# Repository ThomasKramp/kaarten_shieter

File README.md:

# kaarten_shieter
The documentation can be found in the .

The PDF was generated using:
- The PDF version of the .md file .
- An online md to pdf converter

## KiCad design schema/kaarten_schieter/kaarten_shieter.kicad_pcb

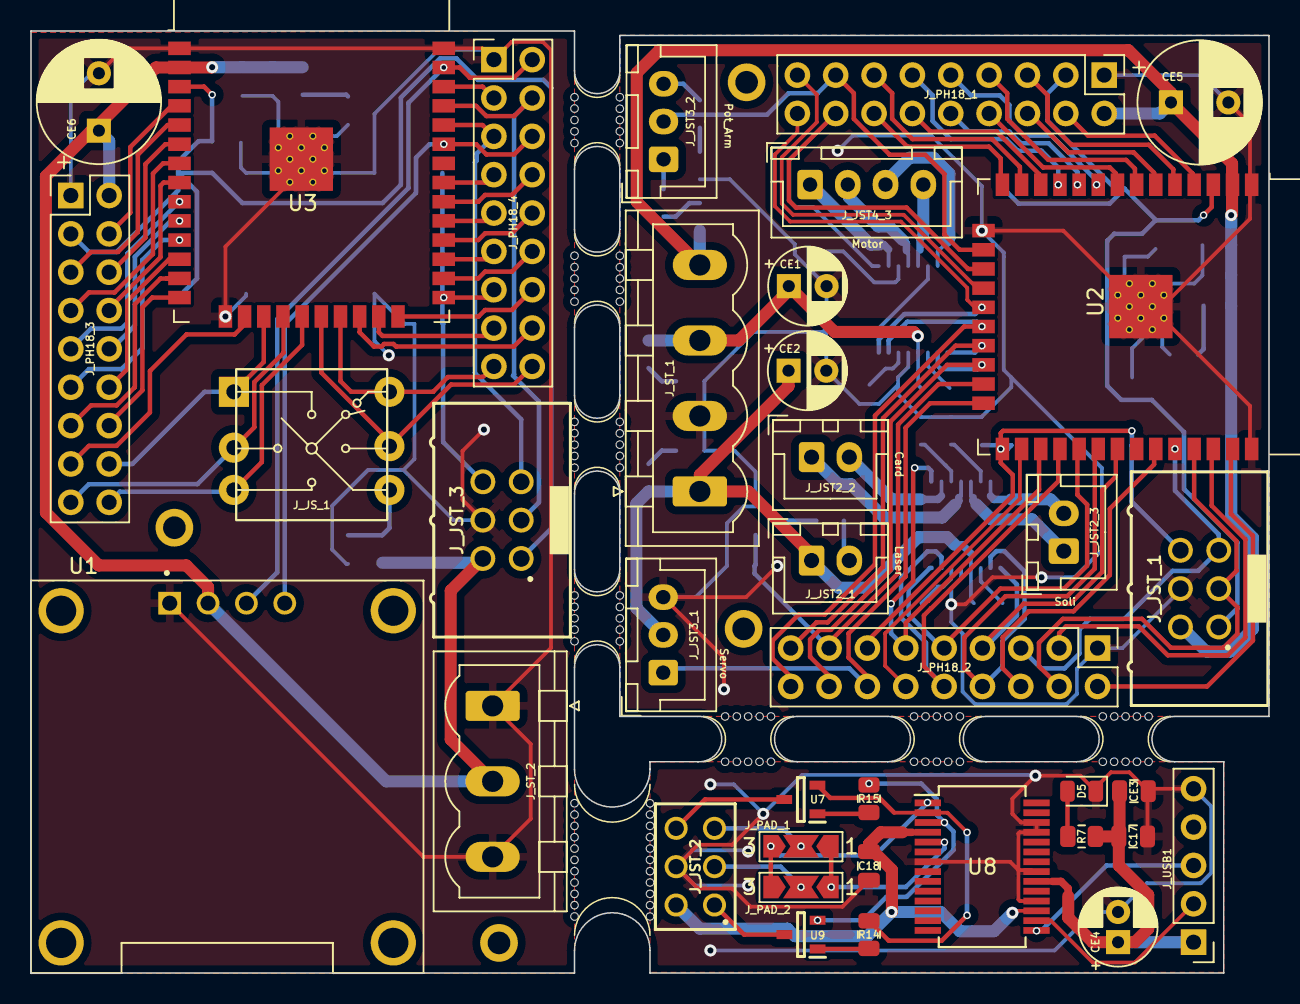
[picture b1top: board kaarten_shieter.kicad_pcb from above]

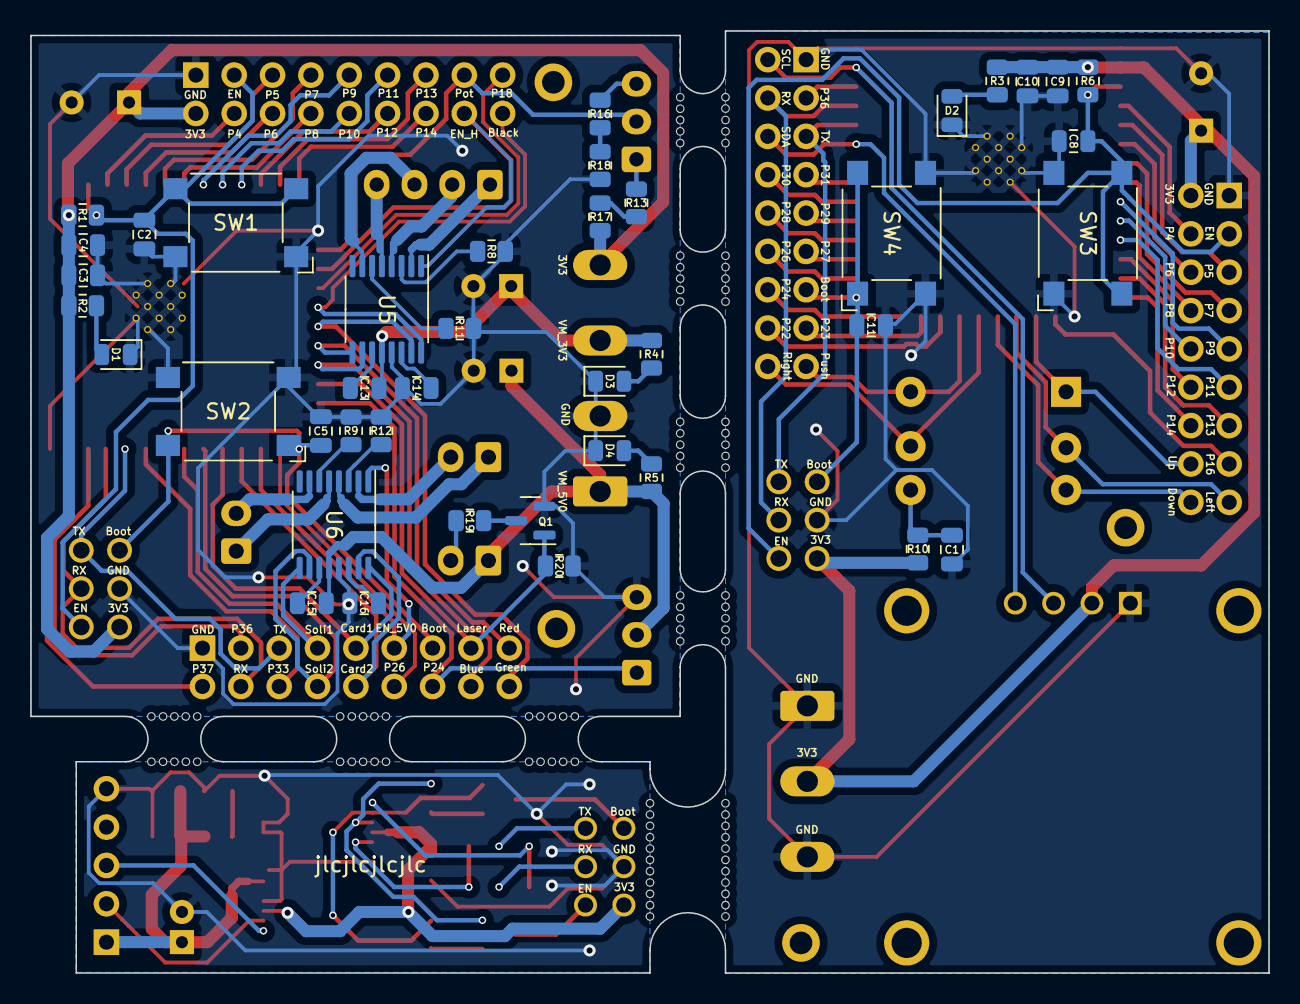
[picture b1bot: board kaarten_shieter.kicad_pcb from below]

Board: 2 copper layers, 82.0 x 62.4 mm, 86 parts (41 on the bottom side), 115 nets.

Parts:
C1, C2, C4, C5, C8, C10, C11: 0u1; C_0805_2012Metric
C3, C9: 22u; C_0805_2012Metric
C13, C15: 0u01; C_0805_2012Metric
C14, C16: 2u2; C_0805_2012Metric
C17, C18: 100n; C_0805_2012Metric
CE1, CE2: 10u; CP_Radial_D5.0mm_P2.50mm
CE3: 10n; C_0805_2012Metric
CE4: 4u7; CP_Radial_D5.0mm_P2.00mm
CE5, CE6: 470u; CP_Radial_D8.0mm_P3.80mm
D1, D2, D3, D4, D5: LED; LED_0805_2012Metric
J_JST2_1, J_JST2_2, J_JST2_3: Conn_01x02_Male; JST_XH_B2B-XH-A_1x02_P2.50mm_Vertical
J_JST3_1, J_JST3_2: Conn_01x03_Male; JST_XH_B3B-XH-A_1x03_P2.50mm_Vertical
J_JST4_3: Conn_01x04_Male; JST_XH_B4B-XH-A_1x04_P2.50mm_Vertical
J_JST_1, J_JST_3: Conn_02x03_Odd_Even; 61200621621
J_JST_2: Conn_02x03_Odd_Even; 61300621821
J_JS_1: Conn_02x03_Counter_Clockwise; JS_SKQUCAA010
J_PAD_1, J_PAD_2: Conn_01x03; SolderJumper-3_P2.0mm_Open_TrianglePad1.0x1.5mm_NumberLabels
J_PH18_1, J_PH18_2, J_PH18_3, J_PH18_4: Conn_02x09_Odd_Even; PinHeader_2x09_P2.54mm_Vertical
J_ST_1: Screw_Terminal_01x04; PhoenixContact_MSTBVA_2,5_4-G_1x04_P5.00mm_Vertical
J_ST_2: Screw_Terminal_01x03; PhoenixContact_MSTBVA_2,5_3-G_1x03_P5.00mm_Vertical
J_USB1: Conn_01x05_Male; PinHeader_1x05_P2.54mm_Vertical
Q1: 2N7002; SOT-23
R1, R6, R10: 10K; R_0805_2012Metric
R2, R3, R4: 1K5; R_0805_2012Metric
R5, R7: 2K; R_0805_2012Metric
R8, R9, R11, R12: 200m; R_0805_2012Metric
R13, R16, R17, R18, R19: R; R_0805_2012Metric
R14, R15: 10k; R_0805_2012Metric
R20: 1M; R_0805_2012Metric
SW1, SW2, SW3, SW4: SW_Push; SW_SPST_Omron_B3FS-100xP
U1: DM-OLED096-636; MODULE_DM-OLED096-636
U2, U3: ESP32-WROOM-32
U5, U6: DRV8833PW; TSSOP-16_4.4x5mm_P0.65mm
U7, U9: BCW71; SOT95P230X110-3N
U8: FT232RL; SSOP-28_5.3x10.2mm_P0.65mm
mouse-bite-5mm-slot, mouse-bite-5mm-slot#3, mouse-bite-5mm-slot#4, mouse-bite-5mm-slot#5, mouse-bite-5mm-slot#6, mouse-bite-5mm-slot#7, mouse-bite-5mm-slot#8: VAL**; mouse-bite-3mm-slot
mouse-bite-5mm-slot#2: VAL**; mouse-bite-5mm-slot

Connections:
3V3_M: C3.1, C4.1, CE5.1, J_JST_1.2, J_PH18_1.2, J_ST_1.4, R1.1, R2.1, R17.1, U2.2 (VDD)
3V3_P: C18.2, J_JST_2.2, U8.4 (VCCIO), U8.17 (3V3OUT)
3V3_R: C9.1, C10.1, CE6.1, J_JST_3.2, J_PH18_3.2, J_ST_2.2, R3.1, R6.1, R10.1, U1.2 (VCC_IN), U3.2 (VDD)
5V0_P: C17.1, CE3.1, CE4.1, J_USB1.1, R7.1, U8.20 (VCC)
BOOT_M: C5.1, J_JST_1.6, J_PH18_2.13, SW2.1, U2.25 (IO0)
BOOT_P: J_JST_2.6, U7.3 (C)
BOOT_R: C11.1, J_JST_3.6, J_PH18_4.13, SW4.1, U3.25 (IO0)
Black: J_JST4_3.1, U5.2 (AOUT1)
Blue: J_JST4_3.4, U5.5 (BOUT2)
CENTER_JS: J_JS_1.6, J_PH18_4.17, U3.21 (SDO/SD0)
COM_JS: C1.1, J_JS_1.4, R10.2
Card1: J_JST2_2.2, U6.2 (AOUT1)
Card2: J_JST2_2.1, U6.4 (AOUT2)
DOWN_JS: J_JS_1.3, J_PH18_3.18, U3.19 (SCS/CMD)
EN_Card: J_PH18_2.11, U2.27 (IO16), U6.1 (nSLEEP)
EN_Hori: J_PH18_1.16, U2.17 (SHD/SD2), U5.1 (nSLEEP)
EN_M: C2.1, J_JST_1.1, J_PH18_1.3, R1.2, SW1.2, U2.3 (EN)
EN_P: J_JST_2.1, U9.3 (C)
EN_R: C8.1, J_JST_3.1, J_PH18_3.3, R6.2, SW3.2, U3.3 (EN)
GND_M: C2.2, C3.2, C4.2, C5.2, C14.1, C16.1, CE1.2, CE2.2, CE5.2, D1.1 (K), D3.1 (K), D4.1 (K), J_JST3_1.3, J_JST_1.4, J_PH18_1.1, J_PH18_2.1, J_ST_1.2, Q1.2 (S), R8.2, R9.2, R11.2, R12.2, R18.1, R20.2, SW1.1, SW2.2, U2.1 (GND), U2.15 (GND), U2.38 (GND), U2.39 (GND), U5.13 (GND), U6.13 (GND)
GND_P: C17.2, C18.1, CE3.2, CE4.2, D5.1 (K), J_JST_2.4, J_USB1.5, U8.7 (GND), U8.18 (GND), U8.21 (GND), U8.25 (AGND), U8.26 (TEST)
GND_R: C1.2, C8.2, C9.2, C10.2, C11.2, CE6.2, D2.1 (K), J_JST_3.4, J_PH18_3.1, J_PH18_4.1, J_ST_2.1, J_ST_2.3, SW3.1, SW4.2, U1.1 (GND), U3.1 (GND), U3.15 (GND), U3.38 (GND), U3.39 (GND)
Green: J_JST4_3.2, U5.4 (AOUT2)
LEFT_JS: J_JS_1.2, J_PH18_3.17, U3.18 (SWP/SD3)
Laser: J_PH18_2.15, Q1.1 (G), R20.1, U2.23 (IO15)
Motor_Card_IN1: J_PH18_2.9, U2.29 (IO5), U6.16 (AIN1)
Motor_Card_IN2: J_PH18_2.10, U2.28 (IO17), U6.15 (AIN2)
Motor_Hori_Black: J_PH18_1.18, U2.19 (SCS/CMD), U5.16 (AIN1)
Motor_Hori_Blue: J_PH18_2.16, U2.22 (SDI/SD1), U5.10 (BIN2)
Motor_Hori_Green: J_PH18_2.18, U2.20 (SCK/CLK), U5.15 (AIN2)
Motor_Hori_Red: J_PH18_2.17, U2.21 (SDO/SD0), U5.9 (BIN1)
Motor_Soli_IN1: J_PH18_2.7, U2.31 (IO19), U6.9 (BIN1)
Motor_Soli_IN2: J_PH18_2.8, U2.30 (IO18), U6.10 (BIN2)
unnamed: C13.2, U5.11 (VCP)
unnamed: C14.2, U5.14 (VINT)
unnamed: C15.2, U6.11 (VCP)
unnamed: C16.2, U6.14 (VINT)
unnamed: D1.2 (A), R2.2
unnamed: D2.2 (A), R3.2
unnamed: D3.2 (A), R4.2
unnamed: D4.2 (A), R5.2
unnamed: D5.2 (A), R7.2
unnamed: J_JST2_1.2, R19.2
unnamed: J_JST3_2.1, R13.2
unnamed: J_JST3_2.3, R16.2
unnamed: Q1.3 (D), R19.1
unnamed: R8.1, U5.3 (AISEN)
unnamed: R9.1, U6.6 (BISEN)
unnamed: R11.1, U5.6 (BISEN)
unnamed: R12.1, U6.3 (AISEN)
unnamed: R13.1, R17.2
unnamed: R14.1, U9.1 (B)
unnamed: R15.1, U7.1 (B)
unnamed: R16.1, R18.2
PIN4_M: J_PH18_1.4, U2.4 (SENSOR_VP)
PIN4_R: J_PH18_3.4, U3.4 (SENSOR_VP)
PIN5_M: J_PH18_1.5, U2.5 (SENSOR_VN)
PIN5_R: J_PH18_3.5, U3.5 (SENSOR_VN)
PIN6_M: J_PH18_1.6, U2.6 (IO34)
PIN6_R: J_PH18_3.6, U3.6 (IO34)
PIN7_M: J_PH18_1.7, U2.7 (IO35)
PIN7_R: J_PH18_3.7, U3.7 (IO35)
PIN8_M: J_PH18_1.8, U2.8 (IO32)
PIN8_R: J_PH18_3.8, U3.8 (IO32)
PIN9_M: J_PH18_1.9, U2.9 (IO33)
PIN9_R: J_PH18_3.9, U3.9 (IO33)
PIN10_M: J_PH18_1.10, U2.10 (IO25)
PIN10_R: J_PH18_3.10, U3.10 (IO25)
PIN11_M: J_PH18_1.11, U2.11 (IO26)
PIN11_R: J_PH18_3.11, U3.11 (IO26)
PIN12_M: J_PH18_1.12, U2.12 (IO27)
PIN12_R: J_PH18_3.12, U3.12 (IO27)
PIN13_M: J_PH18_1.13, U2.13 (IO14)
PIN13_R: J_PH18_3.13, U3.13 (IO14)
PIN14_M: J_PH18_1.14, U2.14 (IO12)
PIN14_R: J_PH18_3.14, U3.14 (IO12)
PIN16_M: J_JST3_2.2, J_PH18_1.15, U2.16 (IO13)
PIN16_R: J_PH18_3.15, U3.16 (IO13)
PIN17_R: J_JS_1.1, J_PH18_3.16, U3.17 (SHD/SD2)
PIN18_M: J_PH18_1.17, U2.18 (SWP/SD3)
PIN20_R: J_JS_1.5, J_PH18_4.18, U3.20 (SCK/CLK)
PIN22_R: J_PH18_4.16, U3.22 (SDI/SD1)
PIN23_R: J_PH18_4.15, U3.23 (IO15)
PIN24_M: J_JST3_1.1, J_PH18_2.14, U2.24 (IO2)
PIN24_R: J_PH18_4.14, U3.24 (IO2)
PIN26_M: J_PH18_2.12, U2.26 (IO4)
PIN26_R: J_PH18_4.12, U3.26 (IO4)
PIN27_R: J_PH18_4.11, U3.27 (IO16)
PIN28_R: J_PH18_4.10, U3.28 (IO17)
PIN29_R: J_PH18_4.9, U3.29 (IO5)
PIN30_R: J_PH18_4.8, U3.30 (IO18)
PIN31_R: J_PH18_4.7, U3.31 (IO19)
PIN33_M: J_PH18_2.6, U2.33 (IO21)
PIN33_R: J_PH18_4.6, U1.4 (SDA), U3.33 (IO21)
PIN34_M: J_JST_1.5, J_PH18_2.5, U2.34 (RXD0/IO3)
PIN34_R: J_JST_3.5, J_PH18_4.5, U3.34 (RXD0/IO3)
PIN35_M: J_JST_1.3, J_PH18_2.4, U2.35 (TXD0/IO1)
PIN35_R: J_JST_3.3, J_PH18_4.4, U3.35 (TXD0/IO1)
PIN36_M: J_PH18_2.3, U2.36 (IO22)
PIN36_R: J_PH18_4.3, U3.36 (IO22)
PIN37_M: J_PH18_2.2, U2.37 (IO23)
PIN37_R: J_PH18_4.2, U1.3 (SCL), U3.37 (IO23)
Red: J_JST4_3.3, U5.7 (BOUT1)
Soli1: J_JST2_3.2, U6.7 (BOUT1)
Soli2: J_JST2_3.1, U6.5 (BOUT2)
UART_DTR_P: R14.2, U7.2 (E), U8.2 (DTR)
UART_RDX_P: J_PAD_1.1, J_PAD_2.1, U8.5 (RXD)
UART_RTS_P: R15.2, U8.3 (RTS), U9.2 (E)
UART_RX: J_JST_2.3, J_PAD_2.2
UART_TDX_P: J_PAD_1.3, J_PAD_2.3, U8.1 (TXD)
UART_TX: J_JST_2.5, J_PAD_1.2
USBDM: J_USB1.2, U8.16 (USBD-)
USBDP: J_USB1.3, U8.15 (USBD+)
VM_3V3: C13.1, CE1.1, J_ST_1.3, R4.1, U5.12 (VM)
VM_5V0: C15.1, CE2.1, J_JST2_1.1, J_JST3_1.2, J_ST_1.1, R5.1, U6.12 (VM)

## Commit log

2024-11-21 version 1
2024-11-21 version 2
2024-11-21 version 3
2024-11-21 version 4
2024-11-21 add casing files
2024-11-21 documentation
2024-11-24 casing
2025-01-09 docs to english
2025-01-09 picture edit
2025-01-09 problems and solutions start
2025-01-10 problems and solutions add subsections
2025-01-11 code to links
2025-01-11 link corrections
2025-01-11 add code and demo
2025-01-11 add last problem and solution
2025-01-11 relative path page
2025-01-11 relative path corrections
2025-01-11 url path md
2025-01-11 url path corrections
2025-01-11 final edits
